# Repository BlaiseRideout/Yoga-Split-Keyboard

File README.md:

# Yoga Split Keyboard

A ZMK-powered, low-profile, wireless columnar keyboard that drops onto the lower screen of a
**Lenovo Yoga Book 9i Gen 9 (13IMU9)** in place of the bundled keyboard. It has the same
295.3 × 113 mm footprint and magnet pockets for docking.

* **Layout (default):** 3 × 6 columnar keys plus 3 thumb keys per side (42 keys, Corne-style), with
  each half's key block angled 10° inward. Kailh Choc v1 at 18 × 17 mm spacing. Files:
  `ergogen-3row/`, `pcb-3row/`, `case/stl-3row/`, firmware `yoga3_*`
  ([details](docs/design.md#3-row-variant-angled-key-blocks-ergogen-3row-pcb-3row)).
* **4-row option:** the original 6 × 4 grid with a number row (54 keys), in `ergogen/`, `pcb/`,
  `case/stl/` and the `yoga_*` firmware. The [fit study](docs/design.md#fit-study-4-rows-fit) shows
  why it fits. The MX-spaced and SMT (hotswap) boards exist for the 4-row layout only so far.
* **Controller and display:** a nice!nano v2 with a nice!view in the centre gap of each half, or
  three cheap status LEDs instead of the screen ([details](docs/design.md#status-leds-instead-of-screens)).
  The monolithic version has one of each in the middle.
* **Two variants built from one ergogen config:**
  * **Split.** Two halves that join with 6 × 3 mm magnets and steel dowels for docking, or come
    apart for the desk.
  * **Monolithic.** One PCB and one controller, for comparison.
* **MX-spaced variant:** the same layout at 19.05 mm for Choc v2 / KS-33 switches with MX-stem
  keycaps also fits ([details](docs/design.md#mx-spaced-variant-ergogen-mx-pcb-mx-case-mx)). It uses
  the same firmware.
* **Wired or wireless:** USB-C on the left half (or the mono) works as a wired keyboard, with
  Bluetooth otherwise. `&out OUT_TOG` switches by hand ([details](docs/design.md#wired-usb-mode)).
* **One cable charges both halves** while they're joined, through a magnetic pogo link in the join
  wall ([how](docs/design.md#charging-both-halves-from-one-cable-split-only)).
* **Two PCB builds, THT and SMT:** all through-hole (default, no SMD soldering and no JLC assembly) or
  hotswap with JLC assembly (`hotswap-smd/`). Both are fully diode-per-key for n-key rollover.
* **Cost:** see [docs/cost-comparison.md](docs/cost-comparison.md). A first 3-row split build is about
  $300 through-hole, delivered to the US including tariffs ($319 for the 4-row, $400 for the 4-row
  hotswap).

## Repository layout

| Path | What |
|---|---|
| `ergogen/config.yaml`, `ergogen/footprints/` | Source of truth for key positions, outlines and all three PCBs (ergogen 4.2.1, KiCad 5 template) |
| `pcb/{left,right,mono}/` | KiCad boards (KiCad 7 format, opens in 7, 8 and 9), placed and autorouted with Freerouting |
| `pcb/gerbers/` | Gerber + drill zips, ready to upload to JLCPCB |
| `ergogen-mx/`, `pcb-mx/` | The MX-spaced (19.05 mm) variant: config, boards, Gerbers. `ergogen-mx/footprints` links to `ergogen/footprints` |
| `ergogen-3row/`, `pcb-3row/`, `case/stl-3row/` | **Default layout.** 3-row: 3 × 6 + 3 per half, key blocks angled 10° inward ([details](docs/design.md#3-row-variant-angled-key-blocks-ergogen-3row-pcb-3row)). Config generated by `tools/make_3row.py`, firmware `yoga3_*` shields |
| `hotswap-smd/` | SMT build: hotswap sockets and SMD parts placed by JLC. Its ergogen configs, KiCad boards, Gerbers, and JLC BOM/CPL (`fab/`), for Choc and MX |
| `ergogen-thin/`, `pcb-thin/`, `case/case_thin.scad`, `case/stl-thin/` | **Thin build**, 7.8 mm to the key tops like the stock keyboard, with a flat top, the caps 1.7 mm proud and the nRF52840 on the PCB instead of a nice!nano: the 3-row layout with Kailh PG1316S scissor-style switches, all parts SMD and machine-assembled, status LEDs instead of the nice!view ([details](docs/thin.md)). Config generated by `tools/make_thin.py` |
| `case/case.scad`, `case/outlines/`, `case/stl/` | Parametric OpenSCAD case, its DXF inputs, and exported STLs (tray and frame for left, right and mono). `-D 'spacing="mx"'` builds the MX variant from `case/outlines-mx/` into `case/stl-mx/` |
| `case/stl*/frame_*_leds.stl` | Top frames with three status-LED holes instead of the nice!view window (`-D 'display="leds"'`) |
| `config/`, `build.yaml` | ZMK user config: shields `yoga_split_left/right` and `yoga_mono`, plus blaise's Cannonkeys Link keymap ported to 54 keys (home row mods, NUM/NAV/FUN/MOUSE/BOARD layers; `tools/port_link_keymap.py`) and build matrix. Builds against the same `caps-word-v0.3` ZMK fork as the Link. `.github/workflows/build-zmk.yml` builds the firmware on push |
| `docs/` | [Design notes and assumptions](docs/design.md), [cost comparison](docs/cost-comparison.md), [PCB review](docs/pcb-review.md), renders |
| `tools/` | Helper scripts: board prep / DSN export, ZMK generation from ergogen points, fab CSVs |

## Status

| Part | State |
|---|---|
| Fit study and layout | Done |
| PCB schematic / netlist and placement (left, right, mono; Choc and MX) | Done |
| PCB routing | Done with Freerouting 2.1. All six boards are 100% routed with 0 DRC errors (only cosmetic silkscreen warnings). GND pours on both layers with stitching vias, 0.25 mm signal / 0.4 mm power tracks. See the [PCB review](docs/pcb-review.md) |
| Gerbers | Done (`pcb/gerbers/`, `pcb-mx/gerbers/`), untested at a fab |
| Case | Done, but untested on a printer |
| Docking magnet positions | **Assumed.** The laptop's EC detects the keyboard magnetically (two positions, no Bluetooth check), so the magnets have to match the stock ones. Map them with viewing film or the dotfiles' `kbdock-test.sh` (see [docs/design.md](docs/design.md#docking)) |
| ZMK firmware | Written, and built by the workflow in CI |

## Regenerating

```sh
npm i -g ergogen@4.2.1
ergogen ergogen -o build/ergogen -d          # PCBs + outlines + points
cp build/ergogen/points/points.yaml tools/   # then:
python3 tools/gen_zmk.py                     # ZMK shields from the key positions
cp build/ergogen/outlines/*.dxf case/outlines/
openscad -D 'variant="left"' -D 'part="tray"' -o case/stl/tray_left.stl case/case.scad
# KiCad python: upgrade the board, set rules, export a DSN for Freerouting
python3 tools/prep_dsn.py build/ergogen/pcbs/left.kicad_pcb pcb/left/yoga_left.kicad_pcb left.dsn
java -jar freerouting-2.1.0.jar --gui.enabled=false -de left.dsn -do left.ses -mp 200
python3 tools/import_ses.py pcb/left/yoga_left.kicad_pcb left.ses left-drc.txt   # adds tracks, runs DRC
python3 tools/add_ground.py pcb/left/yoga_left.kicad_pcb left-drc.txt        # GND pours, stitching vias, DRC
tools/export_gerbers.sh pcb/left/yoga_left.kicad_pcb pcb/gerbers/yoga_left-gerbers.zip
python3 tools/check_matrix.py pcb/*/*.kicad_pcb                 # one diode per key, col2row (NKRO)
# SMT build only: python3 tools/gen_fab.py hotswap-smd/pcb/left/yoga_left.kicad_pcb hotswap-smd/pcb/fab/yoga_left
# MX variant: same steps with ergogen-mx -> build/ergogen-mx, pcb-mx/, case/outlines-mx, -D 'spacing="mx"'
```

## Build notes

1. Order the PCBs at **1.2 mm** thickness. That's what the case stack-up assumes. For the default
   3-row build, use the Gerbers in `pcb-3row/gerbers/`, print `case/stl-3row/`, and flash the
   `yoga3_split_left` / `yoga3_split_right` (or `yoga3_mono`) firmware.
2. THT (default, all through-hole): fit the 1N4148 diodes first, with their bodies flat on the
   **bottom**, the banded end on the square pad. Solder them from the top and trim the leads flush,
   because the gap under the PCB is 2.2 mm. Then fit the switches from the top and solder them from
   the bottom, trimming their pins too. Bend the PTC flat before you solder it. The controller,
   display, battery, power switch, pogo connector and the P4KE10A TVS diode (lying flat, band on
   the round pad) go on the **top**. The 1.5u inner thumb switch sits turned 90° on purpose.
   SMT (`hotswap-smd/`): JLC places the sockets and diodes on the bottom, and the switches
   push in from the top. Solder the TVS diode by hand, as on the THT build.
3. Mount the nice!nano with its components facing the PCB, matching the silkscreen labels. Solder
   it directly, without tall sockets, so the nice!view on top sits flush with the top frame.
   For status LEDs instead of a nice!view, fit the three 3 mm LEDs flat on the PCB (flat side and
   short lead on the square pad) and their resistors on the bottom, and leave the display header empty.
4. Press M2 heat-set inserts into the tray standoffs, and screw the PCB down from the top with
   M2 × 4 low-head screws.
5. Fit the magnetic pogo connector on the split edge of each half: spring pins on the left, flat
   targets on the right. Before closing the case, check both pins line up and that GND matches GND.
6. Glue the docking magnets into the pockets you mapped, and the joining magnets into the split
   faces. Ream the dowel pockets with a 3 mm drill, then glue the 3 × 12 mm dowel pins into the left
   half only ([details](docs/design.md#split-joining)).

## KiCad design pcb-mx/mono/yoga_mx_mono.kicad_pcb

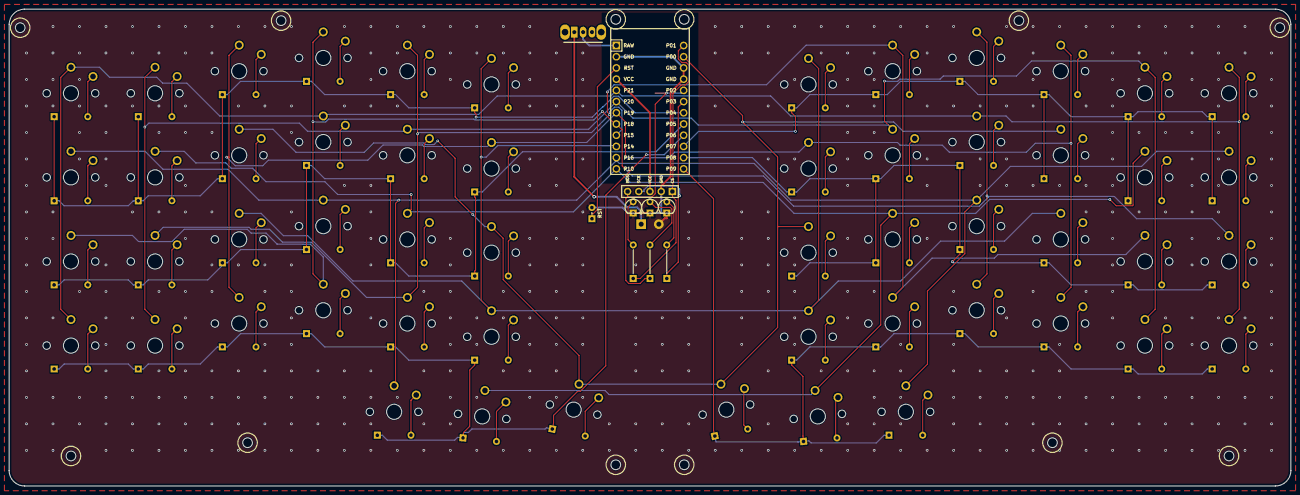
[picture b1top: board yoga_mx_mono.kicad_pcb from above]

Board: 2 copper layers, 290.3 x 108.0 mm, 131 parts (0 on the bottom side), 80 nets.

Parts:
BT1: LiPo; Battery_Pads
D1, D2, D3, D4, D5, D6, D7, D8, D9, D10, D11, D12, D13, D14, D15, D16, D17, D18, D19, D20, D21, D22, D23, D24, D25, D26, D27, D28, D29, D30, D31, D32, D33, D34, D35, D36, D37, D38, D39, D40, D41, D42, D43, D44, D45, D46, D47, D48, D49, D50, D51, D52, D53, D54: 1N4148; D_DO-35_THT
DISP1: nice!view; nice_view
H1, H2, H3, H4, H5, H6, H7, H8, H9, H10, H11, H12: M2; MountingHole_M2
LED1: 3mm LED red; LED_D3.0mm
LED2: 3mm LED green; LED_D3.0mm
LED3: 3mm LED blue; LED_D3.0mm
MCU1: ProMicro
R1: 680R axial DIN0204, on the bottom; THT2_P7.62
R2, R3: 150R axial DIN0204, on the bottom; THT2_P7.62
S1, S2, S3, S4, S5, S6, S7, S8, S9, S10, S11, S12, S13, S14, S15, S16, S17, S18, S19, S20, S21, S22, S23, S24, S25, S26, S27, S28, S29, S30, S31, S32, S33, S34, S35, S36, S37, S38, S39, S40, S41, S42, S43, S44, S45, S46, S47, S48, S49, S50, S51, S52, S53, S54: PG1350
SW1: OS102011MA1QN1; SW_OS102011MA1Q_THT
SW2: reset pads (short or 2-pin tact); THT2_P2.54

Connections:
BAT_P: BT1.1, SW1.1
CS: DISP1.5, MCU1.13, R1.1
GND: BT1.2, DISP1.4, LED1.1, LED2.1, LED3.1, MCU1.2, MCU1.15, MCU1.16, SW2.2
LED_B: LED3.2, R3.2
LED_G: LED2.2, R2.2
LED_R: LED1.2, R1.2
MC0: MCU1.5, S1.2, S4.2, S15.2, S27.2, S30.2, S41.2
MC1: MCU1.6, S5.2, S8.2, S19.2, S31.2, S34.2, S45.2
MC2: MCU1.7, S9.2, S12.2, S23.2, S35.2, S38.2, S49.2
MC3: MCU1.8, S2.2, S13.2, S16.2, S28.2, S39.2, S42.2
MC4: MCU1.9, S6.2, S17.2, S20.2, S32.2, S43.2, S46.2
MC5: MCU1.10, S10.2, S21.2, S24.2, S36.2, S47.2, S50.2
MC6: MCU1.11, S3.2, S14.2, S25.2, S29.2, S40.2, S51.2
MC7: MCU1.12, S7.2, S18.2, S26.2, S33.2, S44.2, S52.2
MC8: MCU1.14, S11.2, S22.2, S37.2, S48.2, S53.2, S54.2
MOSI: DISP1.1, MCU1.17, R2.1
MR0: D3.1, D4.1, D7.1, D8.1, D11.1, D12.1, D16.1, D20.1, D24.1, MCU1.19
MR1: D2.1, D6.1, D10.1, D14.1, D15.1, D18.1, D19.1, D22.1, D23.1, MCU1.20
MR2: D1.1, D5.1, D9.1, D13.1, D17.1, D21.1, D25.1, D26.1, D27.1, MCU1.21
MR3: D30.1, D31.1, D34.1, D35.1, D38.1, D39.1, D43.1, D47.1, D51.1, MCU1.22
MR4: D29.1, D33.1, D37.1, D41.1, D42.1, D45.1, D46.1, D49.1, D50.1, MCU1.23
MR5: D28.1, D32.1, D36.1, D40.1, D44.1, D48.1, D52.1, D53.1, D54.1, MCU1.24
RAW: MCU1.1, SW1.2
RST: MCU1.3, SW2.1
SCK: DISP1.2, MCU1.18, R3.1
VCC: DISP1.3, MCU1.4
home_one: D26.2, S26.1
index_bottom: D17.2, S17.1
index_home: D18.2, S18.1
index_num: D20.2, S20.1
index_top: D19.2, S19.1
inner_bottom: D21.2, S21.1
inner_home: D22.2, S22.1
inner_num: D24.2, S24.1
inner_top: D23.2, S23.1
middle_bottom: D13.2, S13.1
middle_home: D14.2, S14.1
middle_num: D16.2, S16.1
middle_top: D15.2, S15.1
mirror_home_one: D53.2, S52.1
mirror_index_bottom: D44.2, S43.1
mirror_index_home: D45.2, S44.1
mirror_index_num: D47.2, S46.1
mirror_index_top: D46.2, S45.1
mirror_inner_bottom: D48.2, S47.1
mirror_inner_home: D49.2, S48.1
mirror_inner_num: D51.2, S50.1
mirror_inner_top: D50.2, S49.1
mirror_middle_bottom: D40.2, S39.1
mirror_middle_home: D41.2, S40.1
mirror_middle_num: D43.2, S42.1
mirror_middle_top: D42.2, S41.1
mirror_outer_bottom: D28.2, S27.1
mirror_outer_home: D29.2, S28.1
mirror_outer_num: D31.2, S30.1
mirror_outer_top: D30.2, S29.1
mirror_pinky_bottom: D32.2, S31.1
mirror_pinky_home: D33.2, S32.1
mirror_pinky_num: D35.2, S34.1
mirror_pinky_top: D34.2, S33.1
mirror_reachy_one: D54.2, S54.1
mirror_ring_bottom: D36.2, S35.1
mirror_ring_home: D37.2, S36.1
mirror_ring_num: D39.2, S38.1
mirror_ring_top: D38.2, S37.1
mirror_tucky_one: D52.2, S51.1
outer_bottom: D1.2, S1.1
outer_home: D2.2, S2.1
outer_num: D4.2, S4.1
outer_top: D3.2, S3.1
pinky_bottom: D5.2, S5.1
pinky_home: D6.2, S6.1
pinky_num: D8.2, S8.1
pinky_top: D7.2, S7.1
reachy_one: D27.2, S53.1
ring_bottom: D9.2, S9.1
ring_home: D10.2, S10.1
ring_num: D12.2, S12.1
ring_top: D11.2, S11.1
tucky_one: D25.2, S25.1

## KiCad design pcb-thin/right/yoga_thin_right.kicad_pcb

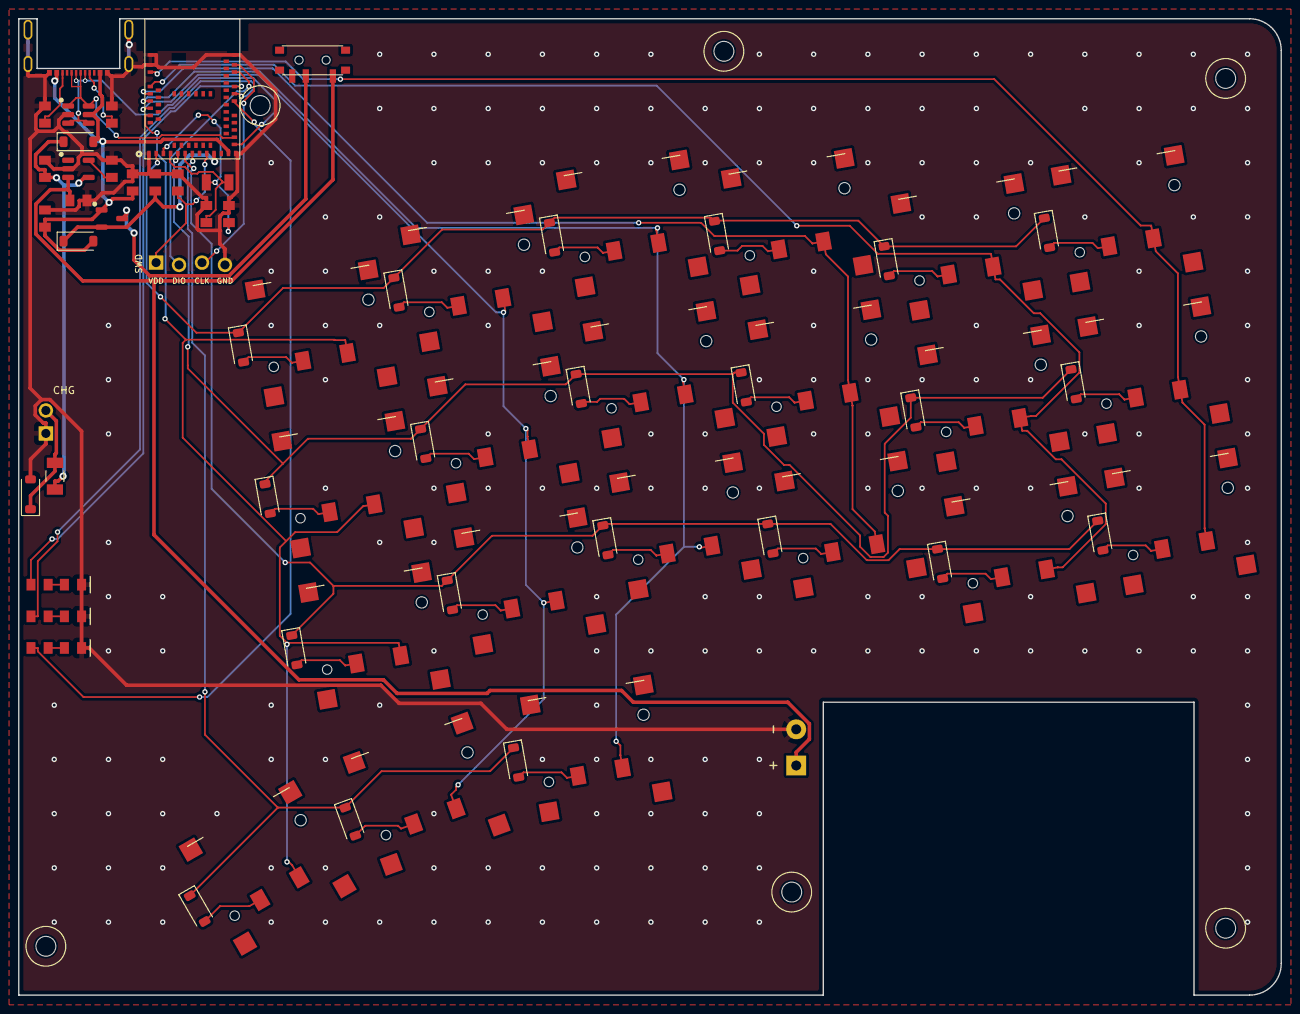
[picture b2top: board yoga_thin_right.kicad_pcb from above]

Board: 2 copper layers, 139.6 x 108.0 mm, 79 parts (0 on the bottom side), 54 nets.

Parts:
BT1: LiPo; Battery_Pads
C1, C2, C3, C4, C5: 4.7uF 0805; SMD_0805
C6, C7: 20pF 0805; SMD_0805
D1, D2, D3, D4, D5, D6, D7, D8, D9, D10, D11, D12, D13, D14, D15, D16, D17, D18, D19, D20, D21, D22: 1N4148W; D_SOD-123
D23, D24: B5819W; D_SOD-123
F1: PTC 0.2A hold 1206; SMD_1206
H1, H2, H3, H4, H5, H6: M2; MountingHole_M2
IC1: MDBT50Q-1MV2; Raytac_MDBT50Q
IC2: USBLC6-2SC6; SOT-23
IC3: TP4054; SOT-23
J1: Pogo 2P female; Pogo_2P_RA_female
J2: USB-C 16P mid-mount; USB_C_C168688
J3: SWD header; SWD_Header_1x04_P2.54
LED1: red LED 0805; SMD_0805_LED
LED2: green LED 0805; SMD_0805_LED
LED3: blue LED 0805; SMD_0805_LED
Q1: AO3401A; SOT-23-3
R1: 680R 0805; SMD_0805
R2, R3: 150R 0805; SMD_0805
R4, R5: 5.1k 0805; SMD_0805
R6: 10k 0805; SMD_0805
R7: 100k 0805; SMD_0805
S1, S2, S3, S4, S5, S6, S7, S8, S9, S10, S11, S12, S13, S14, S15, S16, S17, S18, S19, S20, S21: PG1316S
SW1: MSK-12C02; SW_MSK12C02
Y1: 32.768kHz 12.5pF; Crystal_3215

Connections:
BAT_P: BT1.1, C2.1, IC3.3, SW1.1
C0: IC1.3, S1.2, S2.2, S3.2
C1: IC1.4, S4.2, S5.2, S6.2
C2: IC1.6, S7.2, S8.2, S9.2
C3: IC1.8, S10.2, S11.2, S12.2, S19.2
C4: IC1.10, S13.2, S14.2, S15.2, S20.2
C5: IC1.12, S16.2, S17.2, S18.2, S21.2
CC1: J2.A5, R4.1
CC2: J2.B5, R5.1
CHG_IN: C1.1, D24.1, F1.1, IC3.4
CS: IC1.44, R1.1
GND: BT1.2, C1.2, C2.2, C3.2, C4.2, C5.2, C6.2, C7.2, D22.2, IC1.1, IC1.2, IC1.15, IC1.33, IC1.55, IC2.2, IC3.2, J1.1, J2.A1, J2.S1, J3.4, LED1.2, LED2.2, LED3.2, R4.2, R5.2, R6.2, R7.2
LED_B: LED3.1, R3.2
LED_G: LED2.1, R2.2
LED_R: LED1.1, R1.2
LINK_B: D22.1, F1.2, J1.2
MOSI: IC1.46, R2.1
PROG: IC3.5, R6.1
R0: D3.1, D6.1, D9.1, D12.1, D15.1, D18.1, IC1.16
R1: D2.1, D5.1, D8.1, D11.1, D14.1, D17.1, IC1.20
R2: D1.1, D4.1, D7.1, D10.1, D13.1, D16.1, IC1.22
R3: D19.1, D20.1, D21.1, IC1.24
RAW: C4.1, D23.1, IC1.30, Q1.2
SCK: IC1.48, R3.1
SWDCLK: IC1.53, J3.3
SWDIO: IC1.51, J3.2
SW_OUT: Q1.3, SW1.2
USB_DM: IC1.34, IC2.3, IC2.4, J2.A7, J2.B7
USB_DP: IC1.35, IC2.1, IC2.6, J2.A6, J2.B6
VBUS: C5.1, D23.2, D24.2, IC1.32, IC2.5, J2.A4, Q1.1, R7.1
VDD: C3.1, IC1.28, J3.1
XL1: C6.1, IC1.17, Y1.2
XL2: C7.1, IC1.18, Y1.1
mirror_home_one: D20.2, S20.1
mirror_index_bottom: D13.2, S13.1
mirror_index_home: D14.2, S14.1
mirror_index_top: D15.2, S15.1
mirror_inner_bottom: D16.2, S16.1
mirror_inner_home: D17.2, S17.1
mirror_inner_top: D18.2, S18.1
mirror_middle_bottom: D10.2, S10.1
mirror_middle_home: D11.2, S11.1
mirror_middle_top: D12.2, S12.1
mirror_outer_bottom: D1.2, S1.1
mirror_outer_home: D2.2, S2.1
mirror_outer_top: D3.2, S3.1
mirror_pinky_bottom: D4.2, S4.1
mirror_pinky_home: D5.2, S5.1
mirror_pinky_top: D6.2, S6.1
mirror_reachy_one: D21.2, S21.1
mirror_ring_bottom: D7.2, S7.1
mirror_ring_home: D8.2, S8.1
mirror_ring_top: D9.2, S9.1
mirror_tucky_one: D19.2, S19.1

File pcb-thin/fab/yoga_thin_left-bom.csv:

Comment,Designator,Footprint,LCSC Part #,Qty
Kailh PG1316S switch (consign if LCSC has none),"S9,S21,S6,S16,S19,S13,S3,S14,S17,S11,S4,S20,S7,S5,S2,S15,S10,S18,S1,S8,S12",PG1316S,?,21
"4.7uF 0805 X5R capacitor, 10 V or more","C2,C5,C4,C1,C3",0805,?,5
150R 0805 resistor,"R2,R3",0805,?,2
1N4148W,"D11,D15,D6,D13,D1,D8,D9,D17,D4,D12,D10,D20,D3,D2,D7,D21,D16,D19,D18,D5,D14",SOD-123,C81598,21
red LED 0805,LED1,0805,?,1
10k 0805 resistor,R6,0805,?,1
MSK-12C02 side slide switch,SW1,SW_MSK12C02,C431540?,1
5.1k 0805 resistor,"R5,R4",0805,?,2
green LED 0805,LED2,0805,?,1
B5819W Schottky diode,"D23,D24",SOD-123,?,2
TP4054 Li-ion charger,IC3,SOT-23-5,C32574,1
USBLC6-2SC6 USB ESD clamp,IC2,SOT-23-6,C7519,1
680R 0805 resistor,R1,0805,?,1
blue LED 0805,LED3,0805,?,1
Raytac MDBT50Q-1MV2 nRF52840 module,IC1,SMD-61P,C5118826,1
AO3401A P-MOSFET,Q1,SOT-23,C15127?,1
20pF 0805 C0G capacitor,"C6,C7",0805,?,2
"32.768 kHz crystal 12.5 pF, Epson Q13FC13500004",Y1,3215,C32346,1
100k 0805 resistor,R7,0805,?,1
"SMF5.0A TVS diode, SOD-123FL (5 V link)",D22,SOD-123FL,?,1
USB-C 16P mid-mount receptacle 918-418K2024S40000,J2,USB-C-SMD_16P,C168688,1
"PTC resettable fuse 1206, 0.2 A hold",F1,1206,?,1

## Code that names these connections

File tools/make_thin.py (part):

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        t.append('      # ESD clamp on the exposed charge-link contact (SMF5.0A, SOD-123FL, 5 V standoff)')
        t.append(fp('chg_tvs', 'diode_sod123', X(124.2), 20, 90, '{designator: D, side: F, from: GND, to: LINK_B}'))
    t.append('      # status LEDs (0805, red/green/blue) on the display pins, driven by zmk-rgbled-widget')
    for y, c, net, pin, val in ((3, 'r', 'LED_R', 'CS', '680R'), (6.5, 'g', 'LED_G', 'MOSI', '150R'), (10, 'b', 'LED_B', 'SCK', '150R')):
        t.append(fp(f'led_{c}', 'smd_0805', Y(119.5), y, 0, f'{{designator: LED, led: true, from: {net}, to: GND, value: "{ {"r": "red", "g": "green", "b": "blue"}[c]} LED 0805"}}'))
        t.append(fp(f'led_{c}_res', 'smd_0805', Y(123.2), y, 0, f'{{designator: R, from: {pin}, to: {net}, value: "{val} 0805"}}'))
    t += controller(side, Y, mcu_nets)
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         fp('r_cc2', 'smd_0805', mx - 3.7, 62, 90, r('R', 'CC2', 'GND', '5.1k 0805')),
         '      # Li-ion charger, 100 mA (PROG 10k); its CHRG output is unused. On the split halves it runs from',
         '      # CHG_IN: this half\'s USB 5 V through a Schottky, or the other half\'s over the charge link',
         fp('chg', 'sot23', mx, 56, 0, f'{{designator: IC, value: "TP4054", pins: 5, P2: GND, P3: BAT_P, P4: {cin}, P5: PROG}}'),
         fp('r_prog', 'smd_0805', mx + 3.7, 56, 90, r('R', 'PROG', 'GND', '10k 0805')),
         fp('c_chg', 'smd_0805', mx - 3.7, 56, 90, r('C', cin, 'GND', '4.7uF 0805')),
         fp('c_bat', 'smd_0805', mx, 52.5, 0, r('C', 'BAT_P', 'GND', '4.7uF 0805')),
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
